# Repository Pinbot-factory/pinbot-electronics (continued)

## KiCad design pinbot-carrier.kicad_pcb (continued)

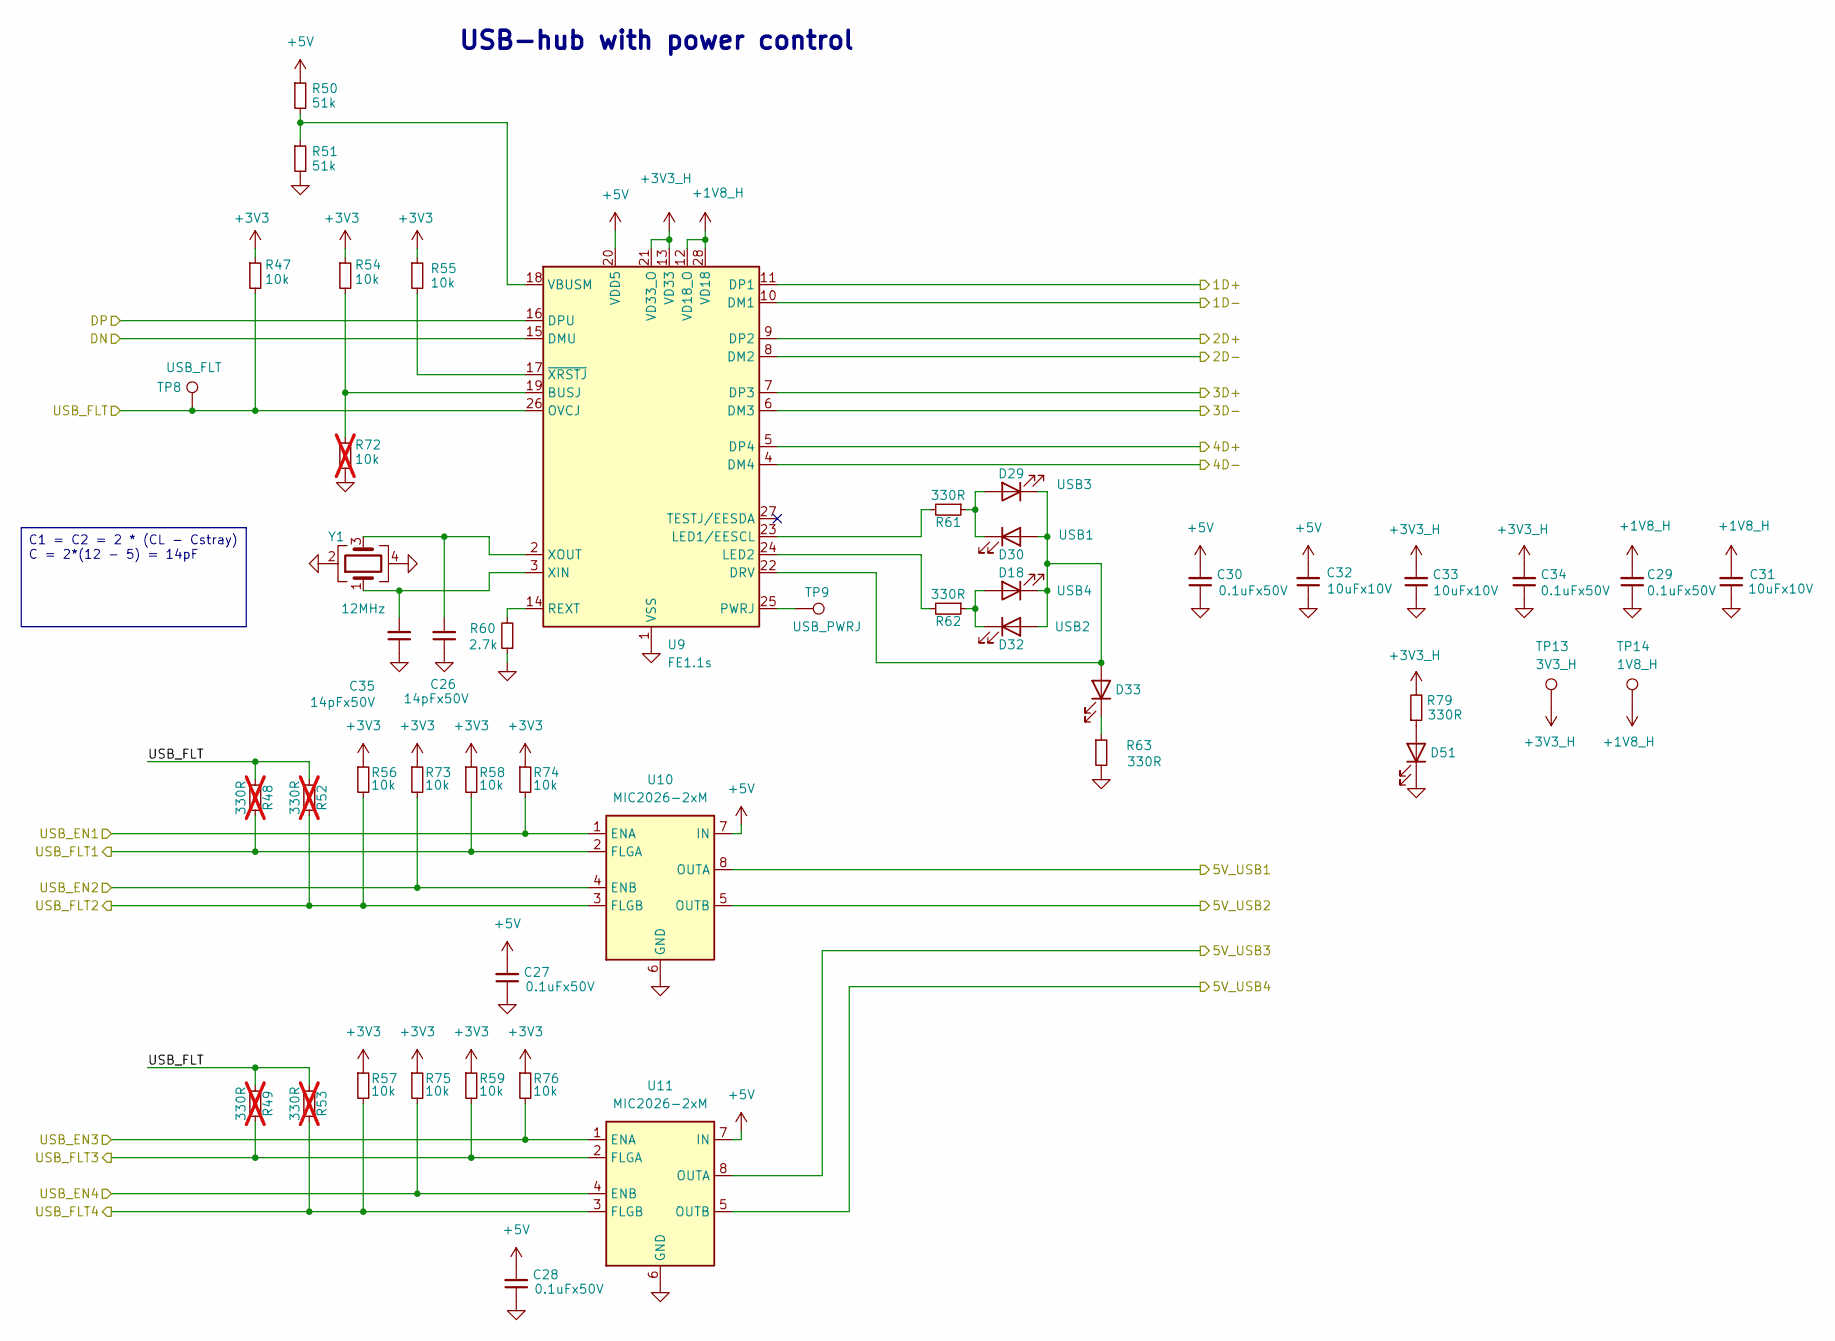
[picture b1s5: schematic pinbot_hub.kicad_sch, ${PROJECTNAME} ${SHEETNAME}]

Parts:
C26, C35: 14pFx50V; C_0603_1608Metric; LCSC Part # C5360816
C27, C28, C29, C30, C34: 0.1uFx50V; C_0603_1608Metric; Mouser Part # CGA3E2X7R1H104M080AA; LCSC Part # C282519
C31, C32, C33: 10uFx10V; C_0603_1608Metric; Mouser Part # GRM188Z71A106MA73J; LCSC Part # C2959727
D18: 19-21/GHC-YR1S2/4T; LED_0603_1608Metric; LCSC Part # C2986048
D29, D30, D32: LTST-S270KGKT; LED_0603_1608Metric_side; Mouser Part # LTST-S270KGKT; LCSC Part # C125113
D33, D51: XL-1608SURC-06; LED_0603_1608Metric; LCSC Part # C965799
R47, R54, R55, R56, R57, R58, R59, R73, R74, R75, R76: 10k; R_0603_1608Metric; Mouser Part # RMC1/16K1002DTP; LCSC Part # C98220
R48, R49, R52, R53: 330R; R_0603_1608Metric; Mouser Part # RMCF0603FT330R; LCSC Part # C23138; not fitted
R50, R51: 51k; R_0603_1608Metric; LCSC Part # C2907180
R60: 2.7k; R_0603_1608Metric; LCSC Part # C13167
R61, R62, R63, R79: 330R; R_0603_1608Metric; Mouser Part # RMCF0603FT330R; LCSC Part # C23138
R72: 10k; R_0603_1608Metric; Mouser Part # RMC1/16K1002DTP; LCSC Part # C98220; not fitted
TP8: USB_FLT; TestPoint_Loop_D1.80mm_Drill1.0mm_Beaded
TP9: USB_PWRJ; TestPoint_Loop_D1.80mm_Drill1.0mm_Beaded
TP13: 3V3_H; TestPoint_Loop_D1.80mm_Drill1.0mm_Beaded
TP14: 1V8_H; TestPoint_Loop_D1.80mm_Drill1.0mm_Beaded
U9: FE1.1s; SSOP-28_3.9x9.9mm_P0.635mm; Manufacturer Part FE1.1S-BSOP28BCN; LCSC Part # C9359
U10, U11: MIC2026-2xM; SOIC-8_3.9x4.9mm_P1.27mm; Mouser Part # MIC2026-2YM
Y1: 12MHz; Crystal_SMD_3225-4Pin_3.2x2.5mm; PartNumber X322512MOB4SI; LCSC Part # C70565

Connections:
+1V8_H: C29.2, C31.2, TP14.1 (1_1), U9.12 (VD18_O), U9.28 (VD18)
+3V3: R47.1, R54.1, R55.1, R56.1, R57.1, R58.1, R59.1, R73.1, R74.1, R75.1, R76.1; also elsewhere on the board
+3V3_H: C33.2, C34.2, R79.2, TP13.1 (1_1), U9.13 (VD33), U9.21 (VD33_O)
+5V: C27.2, C28.2, C30.2, C32.2, R50.1, U9.20 (VDD5), U10.7 (IN), U11.7 (IN); also elsewhere on the board
+5V_USB1: U10.8 (OUTA); also elsewhere on the board
+5V_USB2: U10.5 (OUTB); also elsewhere on the board
+5V_USB3: U11.8 (OUTA); also elsewhere on the board
+5V_USB4: U11.5 (OUTB); also elsewhere on the board
/1D+: U9.11 (DP1); also elsewhere on the board
/1D-: U9.10 (DM1); also elsewhere on the board
/2D+: U9.9 (DP2); also elsewhere on the board
/2D-: U9.8 (DM2); also elsewhere on the board
/3D+: U9.7 (DP3); also elsewhere on the board
/3D-: U9.6 (DM3); also elsewhere on the board
/4D+: U9.5 (DP4); also elsewhere on the board
/4D-: U9.4 (DM4); also elsewhere on the board
/RPI_D+: U9.16 (DPU); also elsewhere on the board
/RPI_D-: U9.15 (DMU); also elsewhere on the board
/USBHUB/USB_FLT: R47.2, R48.1, R49.1, R52.1, R53.1, TP8.1 (1_1), U9.26 (OVCJ)
/USB_EN1: R74.2, U10.1 (ENA); also elsewhere on the board
/USB_EN2: R73.2, U10.4 (ENB); also elsewhere on the board
/USB_EN3: R76.2, U11.1 (ENA); also elsewhere on the board
/USB_EN4: R75.2, U11.4 (ENB); also elsewhere on the board
/USB_FLT1: R48.2, R58.2, U10.2 (FLGA); also elsewhere on the board
/USB_FLT2: R52.2, R56.2, U10.3 (FLGB); also elsewhere on the board
/USB_FLT3: R49.2, R59.2, U11.2 (FLGA); also elsewhere on the board
/USB_FLT4: R53.2, R57.2, U11.3 (FLGB); also elsewhere on the board
GND: C26.1, C27.1, C28.1, C29.1, C30.1, C31.1, C32.1, C33.1, C34.1, C35.1, D51.1 (K), R51.2, R60.1, R63.2, R72.2, U9.1 (VSS), U10.6 (GND), U11.6 (GND), Y1.2, Y1.4; also elsewhere on the board
unnamed: D18.2 (A), D32.1 (K), R62.1
unnamed: D18.1 (K), D29.1 (K), D30.2 (A), D32.2 (A), D33.2 (A), U9.22 (DRV)
unnamed: D29.2 (A), D30.1 (K), R61.1
unnamed: D33.1 (K), R63.1
unnamed: D51.2 (A), R79.1
unnamed: R54.2, R72.1, U9.19 (BUSJ)
unnamed: R61.2, U9.23 (LED1/EESCL)
unnamed: R62.2, U9.24 (LED2)
unnamed: TP9.1 (1_1), U9.25 (PWRJ)
unnamed: R60.2, U9.14 (REXT)
unnamed: R50.2, R51.1, U9.18 (VBUSM)
unnamed: C35.2, U9.3 (XIN), Y1.1
unnamed: C26.2, U9.2 (XOUT), Y1.3
unnamed: R55.2, U9.17 (~XRSTJ)

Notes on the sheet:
USB-hub with power control
C1 = C2 = 2 * (CL - Cstray) С = 2*(12 - 5) = 14pF

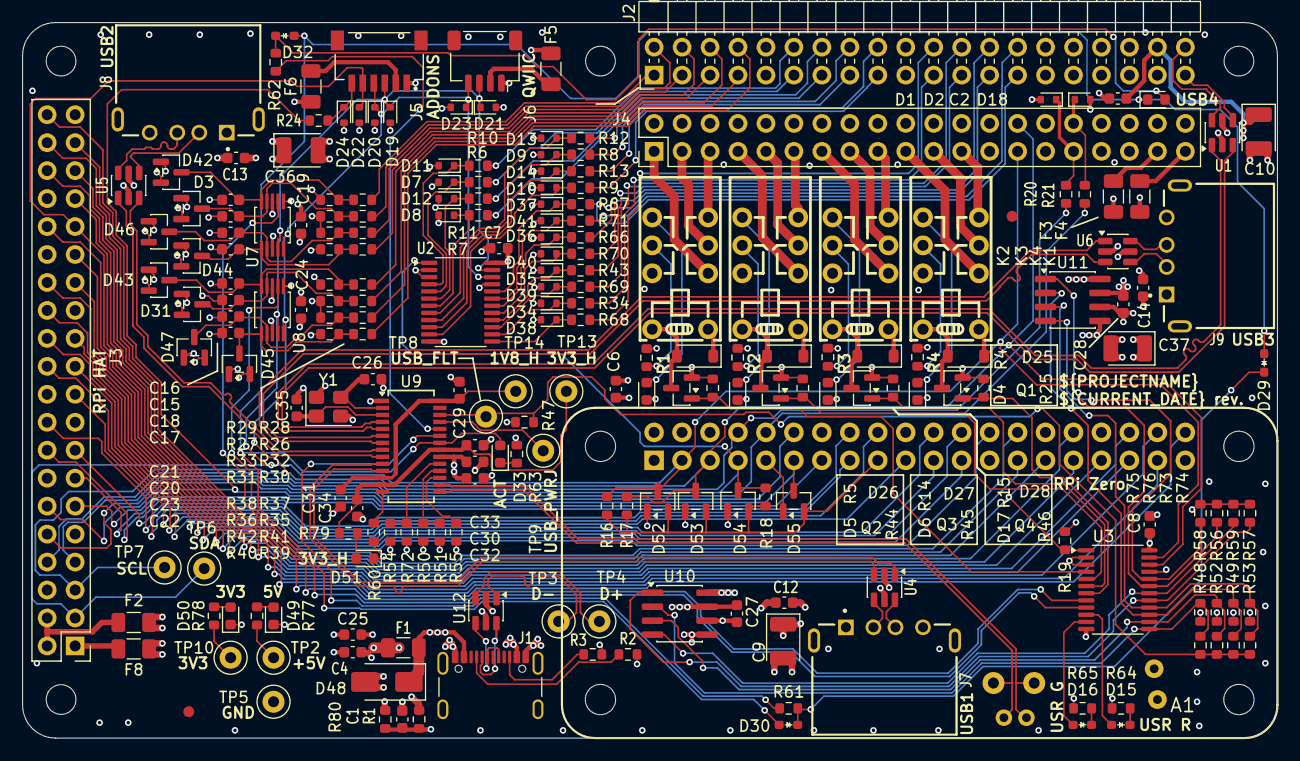
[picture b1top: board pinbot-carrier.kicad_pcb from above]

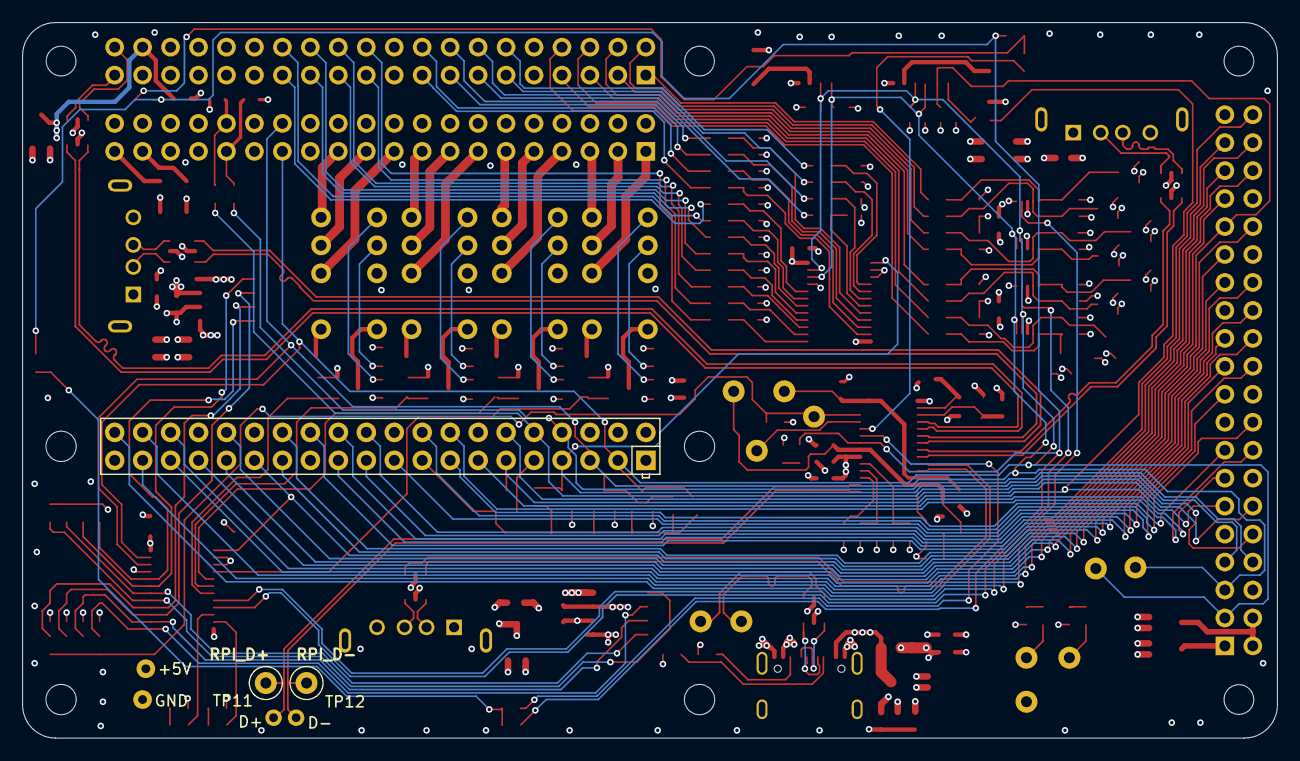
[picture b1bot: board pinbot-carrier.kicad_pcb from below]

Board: 4 copper layers, 114.0 x 65.0 mm, 224 parts (3 on the bottom side), 179 nets.

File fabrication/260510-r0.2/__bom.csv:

Designator,Footprint,Quantity,Value,LCSC Part #
"C10, C36, C37, C9",CP_EIA-3528-21_Kemet-B,4,100uFx10V,C600583
"C12, C13, C14, C15, C16, C17, C18, C19, C2, C20, C21, C22, C23, C24, C27, C28, C29, C30, C34, C4, C7, C8",0603,22,0.1uFx50V,C282519
"C25, C31, C32, C33, C6",0603,5,10uFx10V,C2959727
"C26, C35",0603,2,14pFx50V,C5360816
"D1, D10, D11, D12, D13, D14, D19, D2, D20, D21, D22, D23, D24, D34, D35, D36, D37, D38, D39, D40, D41, D7, D8, D9",D_SOD-523,24,ESD5Z3.3T5G,C22440077
"D15, D33",0603,2,LTST-S270KRKT,C125114
"D16, D29, D30, D32",0603,4,LTST-S270KGKT,C125113
"D17, D18, D4, D5, D6",0603,5,19-21/GHC-YR1S2/4T,C2986048
"D25, D26, D27, D28",D_SOD-123,4,MMSD4148,C11177
"D3, D31, D42, D43, D44, D45, D46, D47, D52, D53, D54, D55",SOT-23,12,BAT54S,C19726
D48,D_SMA,1,SMAJ5.0A,C83329
"D49, D50, D51",0603,3,XL-1608SURC-06,C965799
F1,1206,1,MF-NSMF200-2,C89656
"F2, F3, F4, F5, F6, F8",1206,6,MF-NSMF110-2,C89654
J1,USB_C_Receptacle_GCT_USB4105-xx-A_16P_TopMnt_Horizontal,1,USB4105-GF-A-120,C709358
J5,JST_SM06B-SRSS-TB,1,SM06B-SRSS-TB,C160405
J6,JST_SH_SM04B-SRSS-TB_1x04-1MP_P1.00mm_Horizontal,1,HC-1.0-4PWT,C2845363
"J7, J8, J9",GCT_USB1125-GF-B_REVA,3,USB_A,C5984324
"K1, K2, K3, K4",G6S-2-5V,4,G6S-2-5V,C32776
"Q1, Q2, Q3, Q4",SOT-23,4,2N7002,C81445
"R10, R11, R12, R13, R16, R17, R18, R19, R25, R27, R29, R31, R33, R34, R36, R38, R40, R42, R43, R44, R45, R46, R47, R54, R55, R56, R57, R58, R59, R6, R66, R67, R68, R69, R7, R70, R71, R73, R74, R75, R76, R8, R9",0603,43,10k,C98220
"R14, R15, R20, R21, R4, R5, R61, R62, R63, R64, R65, R77, R78, R79",0603,14,330R,C23138
"R2, R3",0603,2,5.1k,C2907114
R24,0603,1,100R,C2907089
"R26, R28, R30, R32, R35, R37, R39, R41",0603,8,110k,C25805
"R50, R51",0603,2,51k,C2907180
R60,0603,1,2.7k,C13167
R80,0603,1,0,C95177
"U1, U12, U4, U5, U6",SOT-23-6,5,USBLC6-2SC6,C5180249
"U10, U11",SOIC-8_3.9x4.9mm_P1.27mm,2,MIC2026-2xM,C148072
"U2, U3",TSSOP-24_4.4x7.8mm_P0.65mm,2,TCA9535PWR,C22396388
"U7, U8",TSSOP-10_3x3mm_P0.5mm,2,ADS1015IDGS,C193969
U9,SSOP-28_3.9x9.9mm_P0.635mm,1,FE1.1s,C9359
Y1,Crystal_SMD_3225-4Pin_3.2x2.5mm,1,12MHz,C70565

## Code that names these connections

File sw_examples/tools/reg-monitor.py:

"""
Debug helper to monitor Pinbot's IO expanders
in (kinda) real time.
https://github.com/Pinbot-factory
"""
import time
import smbus2 as smbus

CHIPS = {
    "0x20": 0x20,
    "0x21": 0x21,
}

# Registers
INPUT_PORT_0 = 0x00
INPUT_PORT_1 = 0x01
OUTPUT_PORT_0 = 0x02
OUTPUT_PORT_1 = 0x03
POLARITY_PORT_0 = 0x04
POLARITY_PORT_1 = 0x05
CONFIG_PORT_0 = 0x06
CONFIG_PORT_1 = 0x07

bus = smbus.SMBus(1)

# Terminal symbols
RED = "\033[91m"
GRAY = "\033[90m"
YELLOW = "\033[93m"
RESET = "\033[0m"

# Signal map
SIGNALS = {
    (0x20, 0, 0): "GPIO0",
    (0x20, 0, 1): "GPIO1",
    (0x20, 0, 2): "GPIO2",
    (0x20, 0, 3): "GPIO3",
    (0x20, 0, 4): "GPIO4",
    (0x20, 0, 5): "GPIO5",
    (0x20, 0, 6): "GPIO6",
    (0x20, 0, 7): "GPIO7",

    (0x20, 1, 0): "GPIO8",
    (0x20, 1, 1): "GPIO9",
    (0x20, 1, 2): "GPIO10",
    (0x20, 1, 3): "GPIO11",
    (0x20, 1, 4): "GPIO12",
    (0x20, 1, 5): "GPIO13",
    (0x20, 1, 6): "GPIO14",
    (0x20, 1, 7): "GPIO15",

    (0x21, 0, 0): "RELAY1",
    (0x21, 0, 1): "RELAY2",
    (0x21, 0, 2): "RELAY3",
    (0x21, 0, 3): "RELAY4",
    (0x21, 0, 4): "ALERT0",
    (0x21, 0, 5): "ALERT1",
    (0x21, 0, 6): "USR_R",
    (0x21, 0, 7): "USR_G",

    (0x21, 1, 0): "USB_FLT1",
    (0x21, 1, 1): "USB_FLT2",
    (0x21, 1, 2): "USB_FLT3",
    (0x21, 1, 3): "USB_FLT4",
    (0x21, 1, 4): "USB_EN1",
    (0x21, 1, 5): "USB_EN2",
    (0x21, 1, 6): "USB_EN3",
    (0x21, 1, 7): "USB_EN4",
}

ACTIVE_LOW = {
    "USB_FLT1", "USB_FLT2", "USB_FLT3", "USB_FLT4",
    "USB_EN1", "USB_EN2", "USB_EN3", "USB_EN4"
}


def read(addr):
    return {
        "in": (
            bus.read_byte_data(addr, INPUT_PORT_0),
            bus.read_byte_data(addr, INPUT_PORT_1),
        ),
        "out": (
            bus.read_byte_data(addr, OUTPUT_PORT_0),
            bus.read_byte_data(addr, OUTPUT_PORT_1),
        ),
        "pol": (
            bus.read_byte_data(addr, POLARITY_PORT_0),
            bus.read_byte_data(addr, POLARITY_PORT_1),
        ),
        "cfg": (
            bus.read_byte_data(addr, CONFIG_PORT_0),
            bus.read_byte_data(addr, CONFIG_PORT_1),
        ),
    }


def get_bit(v, i):
    return (v >> i) & 1


def bit_string(v):
    return " ".join(str((v >> i) & 1) for i in range(7, -1, -1))


def semantic_state(raw, name):
    """
    Converts physical signal into logical meaning.
    Active-low signals are inverted here.
    """
    if name in ACTIVE_LOW:
        return 0 if raw else 1
    return raw

def sym(v):
    return f"{RED}●{RESET}" if v else f"{GRAY}○{RESET}"


NAME_W = 9


def build_col(addr, port, inp, cfg, offset):
    col = []

    for i in range(4):
        pin = offset + i
        name = SIGNALS.get((addr, port, pin), f"P{port}:{pin}")

        raw = get_bit(inp, pin)
        mode = get_bit(cfg, pin)

        state = semantic_state(raw, name)
        arrow = "←" if mode else "→"

        if name in ACTIVE_LOW:
            col.append(f"{pin} *{name:<{NAME_W}} {sym(state)} {arrow}")
        else:
            col.append(f"{pin} {name:<{NAME_W+1}} {sym(state)} {arrow}")

    return col


# UI LOOP
print("\033[2J", end="")

try:
    while True:
        print("\033[H\033[J", end="")

        for chip_name, addr in CHIPS.items():
            r = read(addr)

            print(f"{YELLOW}TCA9535 @ {chip_name}{RESET}")

            for port in (0, 1):

                inp = r["in"][port]
                out = r["out"][port]
                cfg = r["cfg"][port]
                pol = r["pol"][port]

                col_l = build_col(addr, port, inp, cfg, 0)
                col_r = build_col(addr, port, inp, cfg, 4)

                print(f"Port {port} │ 7 6 5 4 3 2 1 0       ┌──── Bits 0..3 ───┬──── Bits 4..7 ───┐")
                print(f"───────┼──────────────────     │ {col_l[0]:<26}│ {col_r[0]} │")
                print(f"State  │ {bit_string(inp)}       │ {col_l[1]:<26}│ {col_r[1]} │")
                print(f"Latch  │ {bit_string(out)}       │ {col_l[2]:<26}│ {col_r[2]} │")
                print(f"I/O    │ {' '.join('I' if (cfg >> i) & 1 else 'O' for i in range(7, -1, -1))}       │ {col_l[3]:<26}│ {col_r[3]} │")
                print(f"Inv?   │ {' '.join(f'{RED}Y{RESET}' if (pol >> i) & 1 else ' ' for i in range(7, -1, -1))}       └──────────────────┴──────────────────┘")
                print()

        print(f"* - active-low pins, ←/→ - pin in input/output mode, {RED}Y{RESET} - yes, pin inverted, {GRAY}○{RESET}/{RED}●{RESET} - pin inactive/active")
        print()
        print("Press Ctrl+C to exit")
        time.sleep(0.5)

except KeyboardInterrupt:
    print("\nStopped")

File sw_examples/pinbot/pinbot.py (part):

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        # Map lower-case signal name to (TCA attribute name, port, pin)
        self._mapping = {}

        # Register TCA1 signals (GPIO00 to GPIO15)
        for i in range(16):
            port = i // 8
            pin = i % 8
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            self._mapping[f"relay{relay_num}"] = ("io2", 0, i)
            self._mapping[f"relay_{relay_num}"] = ("io2", 0, i)

        self._mapping["alert0"] = ("io2", 0, 4)
        self._mapping["alert_0"] = ("io2", 0, 4)
        self._mapping["alert1"] = ("io2", 0, 5)
        self._mapping["alert_1"] = ("io2", 0, 5)

        self._mapping["usr_r"] = ("io2", 0, 6)
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        # Port 1
        for i in range(4):
            port_num = i + 1
            self._mapping[f"usb_flt{port_num}"] = ("io2", 1, i)
            self._mapping[f"usb_flt_{port_num}"] = ("io2", 1, i)
            self._mapping[f"usb_en{port_num}"] = ("io2", 1, i + 4)
            self._mapping[f"usb_en_{port_num}"] = ("io2", 1, i + 4)
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        try:
            # Read Port 1 from U3 (io2)
            port1_val = self.io2.read_port(1)
            # USB_FLT1-4 are on pins 0-3 of Port 1
            for i in range(4):
                flt_pin = i
                # Active-low: 0 means fault
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
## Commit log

2026-06-09 r0.2 remade from a scratch
2026-06-09 add manufacturing for rev.0.22
2026-06-10 gitignore and power rating updates
2026-06-10 legacy gerbers cleanup
2026-06-29 links to Pinbot mechanical added
